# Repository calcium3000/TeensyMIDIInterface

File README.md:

# Teensy MIDI Interface
MIDI interface for the Teensy 3.2 development board

## Hardware
This board provides standard MIDI IN, OUT, and THRU ports that connect to the [PJRC Teensy 3.2](https://www.pjrc.com/teensy/) development board.  Connections follow the MIDI standard -- i.e. optoisolation on the IN port, standard 5mA signals, etc.  For more information, see the [MIDI 1.0 Specification](https://www.midi.org/specifications/item/the-midi-1-0-specification).

In addition, all pins on the perimeter of the Teensy are broken out for easier access and prototyping.  Footprints for a 5V, 1A regulator and associated components are provided for stand-alone operation.

**Warning:** Disconnect external power source when connected to USB.

### Connections
`MIDI_IN` is connected to `D0/RX1` for use with the `Serial1` library.

`MIDI_OUT` is connected to `D1/TX1`, ditto with `Serial1`.

### License
All source files are released under the [TAPR Open Hardware License](http://tapr.org/ohl).  See `LICENSE.txt` for a copy of the license.

## Software
Provided are two test programs for MIDI input and MIDI output configurations.  Both are adopted from [ PRJC's MIDI Library](https://www.pjrc.com/teensy/td_libs_MIDI.html) page.  More specific examples to come!

### License
All source files are released under the [GNU General Public License](https://www.gnu.org/licenses/gpl.html).  See `LICENSE.txt` for a copy of the license.

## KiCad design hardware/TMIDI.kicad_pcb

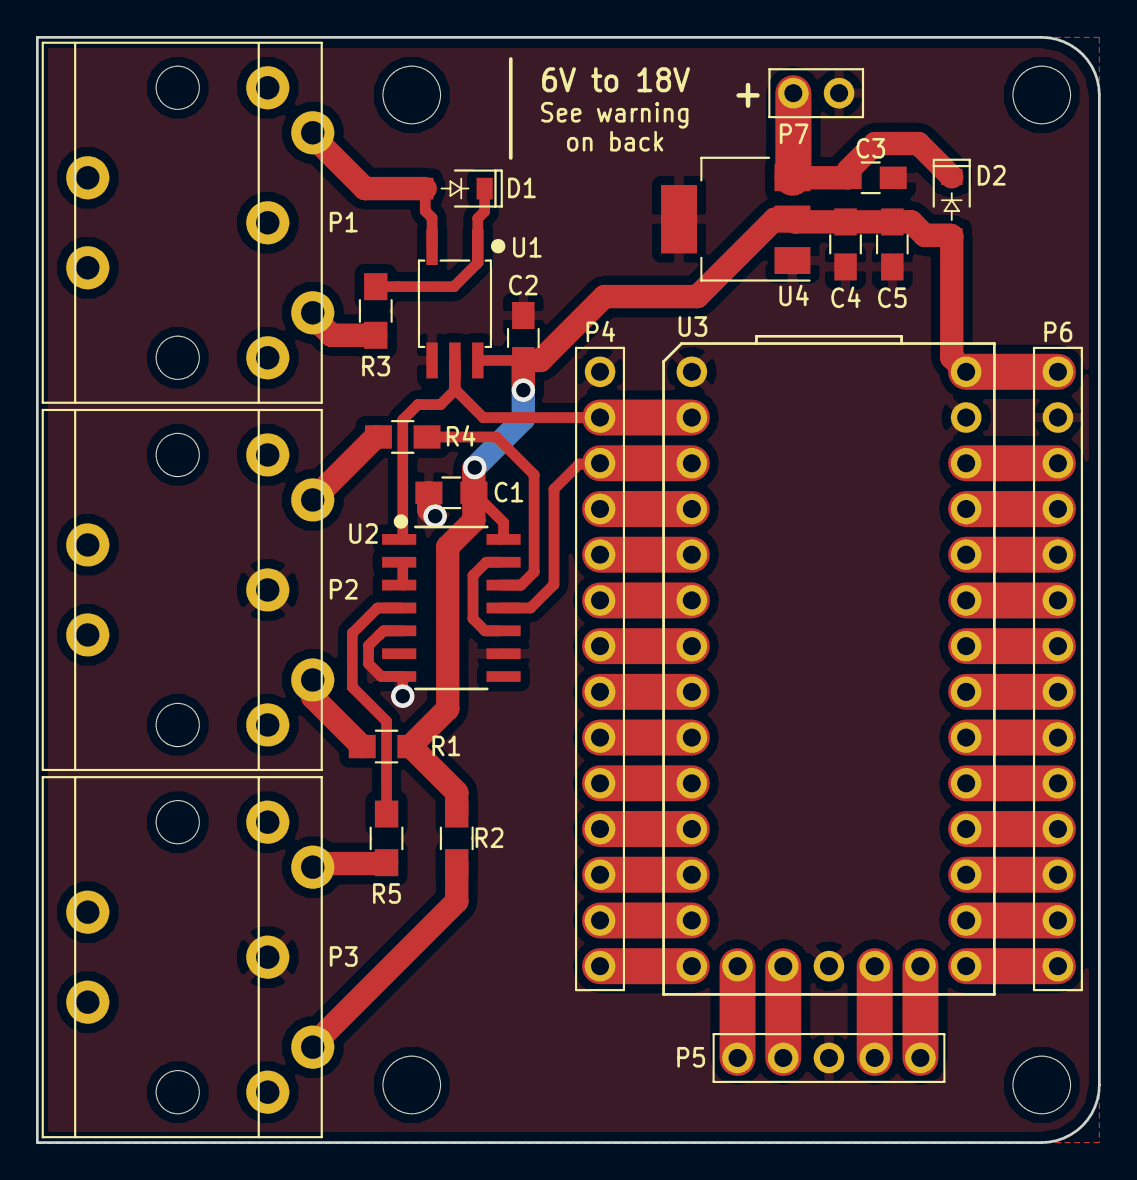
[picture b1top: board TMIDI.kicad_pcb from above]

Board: 2 copper layers, 59.0 x 61.4 mm, 27 parts (0 on the bottom side), 43 nets.

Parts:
C1, C2: 0.1uF; C_0805_HandSoldering
C3: 1uF; C_0805_HandSoldering
C4: 4.7uF; C_0805_HandSoldering
C5: 0805; C_0805_HandSoldering
D1: SCHOTTKY; D_SOD-123
D2: D_Schottky; D_SOD-123
MH0, MH1, MH2, MH3: MountingHole_3.2mm_M3_ISO7380
P1, P2, P3: DIN-5; J_DIN-5_RightAngle
P4, P6: CONN_1x14; J_Conn_1x14_Pitch2.54mm
P5: CONN_1x5; J_Conn_1x5_Pitch2.54mm
P7: CONN_1x2; J_Conn_1x2_Pitch2.54mm
R1, R2, R3, R4, R5: 220R; R_0805_HandSoldering
U1: OPTOISOLATOR; U_SO-5_Width6.3mm_Pitch1.27mm
U2: INVERTER_HEX_SCHMITT; U_SOIC-14_Width3.9mm_Pitch1.27mm
U3: Teensy32; U_Teensy3.2
U4: LDO_4-Pin; U_SOT223-4

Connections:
+5V: C1.1, C2.1, C4.1, C5.1, D2.2, P6.1, R1.1, R2.1, U1.6, U2.14, U3.33, U4.2
/MIN_ISO: D1.1, R3.2, U1.1
/MIN_NEG: D1.2, P1.5, U1.3
/MIN_POS: P1.4, R3.1
/MOUT_INV: U2.10, U2.13
/MOUT_POS: P2.4, R1.2
/MOUT_R: R4.2, U2.12
/MOUT_SIG: P2.5, R4.1
/MTHRU_INV: U2.2, U2.3
/MTHRU_POS: P3.4, R2.2
/MTHRU_R: R5.2, U2.4
/MTHRU_SIG: P3.5, R5.1
/VSUPPLY: C3.1, D2.1, P7.1, U4.3
A14: P5.5, U3.19
D2: P4.4, U3.4
D3: P4.5, U3.5
D4: P4.6, U3.6
D5: P4.7, U3.7
D6: P4.8, U3.8
D7: P4.9, U3.9
D8: P4.10, U3.10
D9: P4.11, U3.11
D10: P4.12, U3.12
D11: P4.13, U3.13
D12: P4.14, U3.14
D13: P6.14, U3.20
D14/A0: P6.13, U3.21
D15/A1: P6.12, U3.22
D16/A2: P6.11, U3.23
D17/A3: P6.10, U3.24
D18/A4: P6.9, U3.25
D19/A5: P6.8, U3.26
D20/A6: P6.7, U3.27
D21/A7: P6.6, U3.28
D22/A8: P6.5, U3.29
D23/A9: P6.4, U3.30
GND: C1.2, C2.2, C3.2, C4.2, C5.2, P2.2, P3.2, P4.1, P5.3, P6.2, P7.2, U1.4, U2.5, U2.7, U2.9, U3.1, U3.17, U3.32, U4.1, U4.4
MIDI_IN: P4.2, U1.5, U2.1, U3.2
MIDI_OUT: P4.3, U2.11, U3.3
PRGM: P5.4, U3.18
VBAT: P5.1, U3.15
VDD_16: P5.2, U3.16
VDD_31: P6.3, U3.31

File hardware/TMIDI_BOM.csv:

QTY,"REF DES",VALUE,FOOTPRINT,DESCRIPTION
2,C1-C2,0.1uF,"0805","Capacitor, MLCC, 100V, 10%, X7R"
1,C3,1uF,"0805","Capacitor, MLCC, 35V, 10%, X7R"
1,C4,4.7uF,"0805","Capacitor, MLCC, 16V, 10%, X7R"
1,C5,DNP,"0805","Capacitor"
2,D1-D2,MBR0580S1-7,SOD-123,"Diode, Schottky, 80V, 500mA"
3,P1-P3,SDS-50J,Through-hole,"Connector, DIN-5, right-angle, PCB mount"
2,"P4,P6",DNP,"Socket strip, 2.54mm pitch","Connector, 1x14"
1,P5,DNP,"Socket strip, 2.54mm pitch","Connector, 1x5"
1,P7,DNP,"Socket strip, 2.54mm pitch","Connector, 1x2"
5,R1-R5,RMCF0805JT220R,"0805","Resistor, thick film, 5%, 0.125W"
1,U1,TLP2361,SOIC-6,"Optoisolator, single channel, logic output"
1,U2,SN74LV14ADR,SOIC-14,"Logic, inverter, hex, Schmitt trigger"
1,U3,Teensy 3.2,Through-hole,"Development board, 72MHz, 256kB flash, 64kB RAM"
1,U4,LDL1117S50R,SOT-223,"Voltage regulator, low-dropout, 5V output, 1.2A"

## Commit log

2018-04-12 Initial commit of v0.1 hardware files
2018-04-12 Updated README to reflect hardware v0.1
2018-04-12 Added license file
2018-04-12 Removed README from hardware branch
2018-04-13 Changed C1-C2 and C4 part numbers, added BOM
2018-04-13 Removed pesky DS_Store file
2018-04-13 Removed unused footprints and another pesky .DS_Store file
2018-04-29 Added MIDI out test program
2018-05-01 Added defines to configure test parameters
2018-05-05 Substituted TLP105 (non-inverted output) optoisolator for TLP2361 (inverted output)
2018-05-05 Updated README with software section
2018-05-05 Added header information to software programs and added software license file
2019-03-04 Updated project to KiCad 5.0, updated optoisolator part number to TLP2361
